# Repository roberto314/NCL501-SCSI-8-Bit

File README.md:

# NCL501-SCSI-8-Bit
Recreation of a bootable ISA 8-Bit SCSI Card.

There is one PAL on the Card (PAL16L8), it is protected unfortunately.
A dump has been done and the equations have been recreated.
They might be wrong.
BIOS EPROM is a 27C64 Type, RAM is not poplated but a 6116 might be used (24-pin Socket).

[Schematic](schematic/NCL501/pdf/NCL501.pdf)

The new card looks like this:

or the real thing:

Changes are:

* active termination or passive Termination possible.
* Term Power with Jumper
* DB25 Connector instead of DB37
* smaller (97.75 x 135mm)

For active Termination the following Parts are needed:

    - C12: 470p Footprint 1206

    - C13, C14: 100n Footprint 1206

    - U11: MIC5219 2.85V Regulator SOT-23-5

This Adapter has some serious shortcomings:

In my Computer (micro8088) it ONLY works with DRQ/DACK 3, ROM @ D8000 and IO @ 330!
IRQ doesn't matter also the RAM onboard is not necessary.

I tested the following Images:

Heads and Sectors working:

spf = sectors/fat, spc = sectors/cluster

* C:  79 / H:8  / S:32 10 MB (FAT12) works
* C:  95 / H:8  / S:32 12 MB (FAT12) works
* C:  39 / H:16 / S:32 10 MB works
* C:  22 / H:15 / S:63 10 MB doesn't work (non-system disk)
* C:  21 / H:16 / S:62 10 MB doesn't work (non-system disk)
* C:  21 / H:16 / S:63 10 MB doesn't work (non-system disk)
* C:  63 / H:16 / S:32 16 MB (FAT12) works
* C:  67 / H:16 / S:32 17 MB (FAT16/4) doesn't work (non-system disk)
* C:  67 / H:16 / S:32 17 MB (FAT16/4) with spf=0x40 instead of 0x100: works
* C: 127 / H:16 / S:32 32 MB (FAT16/4) with spf=0x40 instead of 0x100: works
* C: 135 / H:16 / S:32 33 MB (FAT16/6) with spf=0x60 instead of 0x100: works
* C: 255 / H:16 / S:32 64 MB (FAT16/6) with spf=0x40 instead of 0x100: doesn't work (non-system disk)
* C: 255 / H:16 / S:32 64 MB (FAT16/6) with spf=0x40 instead of 0x100: doesn't work (non-system disk)
* C: 255 / H:16 / S:32 64 MB (FAT16/6) with spf=0x80 instead of 0x100: works
* C: 507 / H:16 / S:32 127 MB (FAT16/6) with spf=0xFF instead of 0x100: doesn't work (non-system disk)
* C: 507 / H:16 / S:32 127 MB (FAT16/6) with spf=0xFE instead of 0x100: doesn't work (non-system disk)
* C: 359 / H:16 / S:32 90 MB (FAT16/6) with spf=0xC0 instead of 0x100, spc=4: doesn't work
* C: 359 / H:16 / S:32 90 MB (FAT16/6) with spf=0xC0 instead of 0x100, spc=8: doesn't work
* C: 183 / H:16 / S:63 90 MB (FAT16/6) with spf=0xC0 instead of 0x100: doesn't work (non-system disk)
* C: 359 / H:16 / S:32 90 MB (FAT16/6) with spf=0xD0 instead of 0x100: doesn't work, hangs
* C: 359 / H:16 / S:32 90 MB (FAT16/6) with spf=0xE0 instead of 0x100: doesn't work, hangs
* C: 479 / H:16 / S:32 120 MB (FAT16/6) with spf=0xF0 instead of 0x100: doesn't work (non-system disk)
* C: 511 / H:16 / S:32 128 MB (FAT16/6) with spf=0xC0 instead of 0x100: doesn't work
* C: 511 / H:16 / S:32 128 MB (FAT16/6) with spf=0x80, spc=8 instead of 0x100: works
* C: 515 / H:16 / S:32 129 MB (FAT16/6) with spf=0xC0 instead of 0x100: doesn't work
* C: 763 / H:16 / S:32 191 MB (FAT16/6) with spf=0xC0 instead of 0x100: doesn't work
* C: 767 / H:16 / S:32 192 MB (FAT16/6) with spf=0xC0 instead of 0x100: doesn't work
* C:1019 / H:16 / S:32 255 MB (FAT16/6) with spf=0x80,spc=16  works
* C:1023 / H:16 / S:32 256 MB (FAT16/6) with spf=0x80,spc=16  works
* C: 741 / H:16 / S:33 191 MB (FAT16/6) with spf=0xC0 instead of 0x100: doesn't work (non-system disk)
* C: 1006 / H:14 / S:48 330 MB (FAT16/6) with spf=0xC0 instead of 0x100: doesn't work (non-system disk)
* C:  510 / H:16 / S:48 191 MB (FAT16/6) with spf=0xC0 instead of 0x100: doesn't work (non-system disk)
* C:  620 / H:16 / S:62 300 MB (FAT16/6) with spf=0x100,spc=16: doesn't work (non-system disk)
* C:  620 / H:16 / S:62 300 MB (FAT16/6) with spf=0x80,spc=32: doesn't work (non-system disk)
* C:  620 / H:16 / S:62 300 MB (FAT16/6) with spf=0x80,spc=32: doesn't work (non-system disk)
* C:  262 / H:16 / S:63 300 MB (FAT16/6) with spf=0xFC,spc=16: doesn't work (non-system disk)
* C:  262 / H:16 / S:63 300 MB (FAT16/6) with spf=0xC0,spc=16: doesn't work (non-system disk)
* C:  514 / H:32 / S:32 257.5 MB (FAT16/6) with spf=0xFC,spc=16  works
* C: 1005 / H:32 / S:32 503 MB (FAT16/6) with spf=0xFC,spc=16  works
* C: 1001 / H:5 / S:52 127 MB (FAT16/6) with spf=0xC0,spc=8 doesn't work (non-system disk)
* C: 1001 / H:5 / S:52 127 MB (FAT16/6) with spf=0xFC,spc=8 doesn't work (non-system disk)
 
* C: 127 / H:16 / S:32 32 MB doesn't work (non-system disk)
* C: 479 / H:8  / S:32 60 MB doesn't work (non-system disk)
* C: 511 / H:8  / S:32 64 MB doesn't work (non-system disk)
* C: 197 / H:32 / S:32 99 MB (FAT16/4) with spf=0xC0 instead of 0x100: doesn't work (non-system disk)
* C:1023 / H:8  / S:32 128 MB doesn't work (non-system disk)
* C:1023 / H:16 / S:32 256 MB doesn't work (non-system disk)
* C:1019 / H:16 / S:32 255 MB doesn't work (non-system disk)
* C: 511 / H:16 / S:32 128 MB doesn't work (non-system disk)
* C: 511 / H:16 / S:32 128 MB (FAT16/4) with spf=0x40 instead of 0x100: doesn't work (non-system disk)
* C: 503 / H:16 / S:32 126 MB (FAT16/4) with spf=0x40 instead of 0x100: doesn't work (non-system disk)

Limits are: 

* spf Value only 8-bit and only some values are possible.
* Size 503MB for now.

The Card can be hacked to be a SUMO SCSI Card with reasonable effort (by omitting U12-14). Then the ASPI Driver ZHA.SYS and ZDRV.SYS will work.

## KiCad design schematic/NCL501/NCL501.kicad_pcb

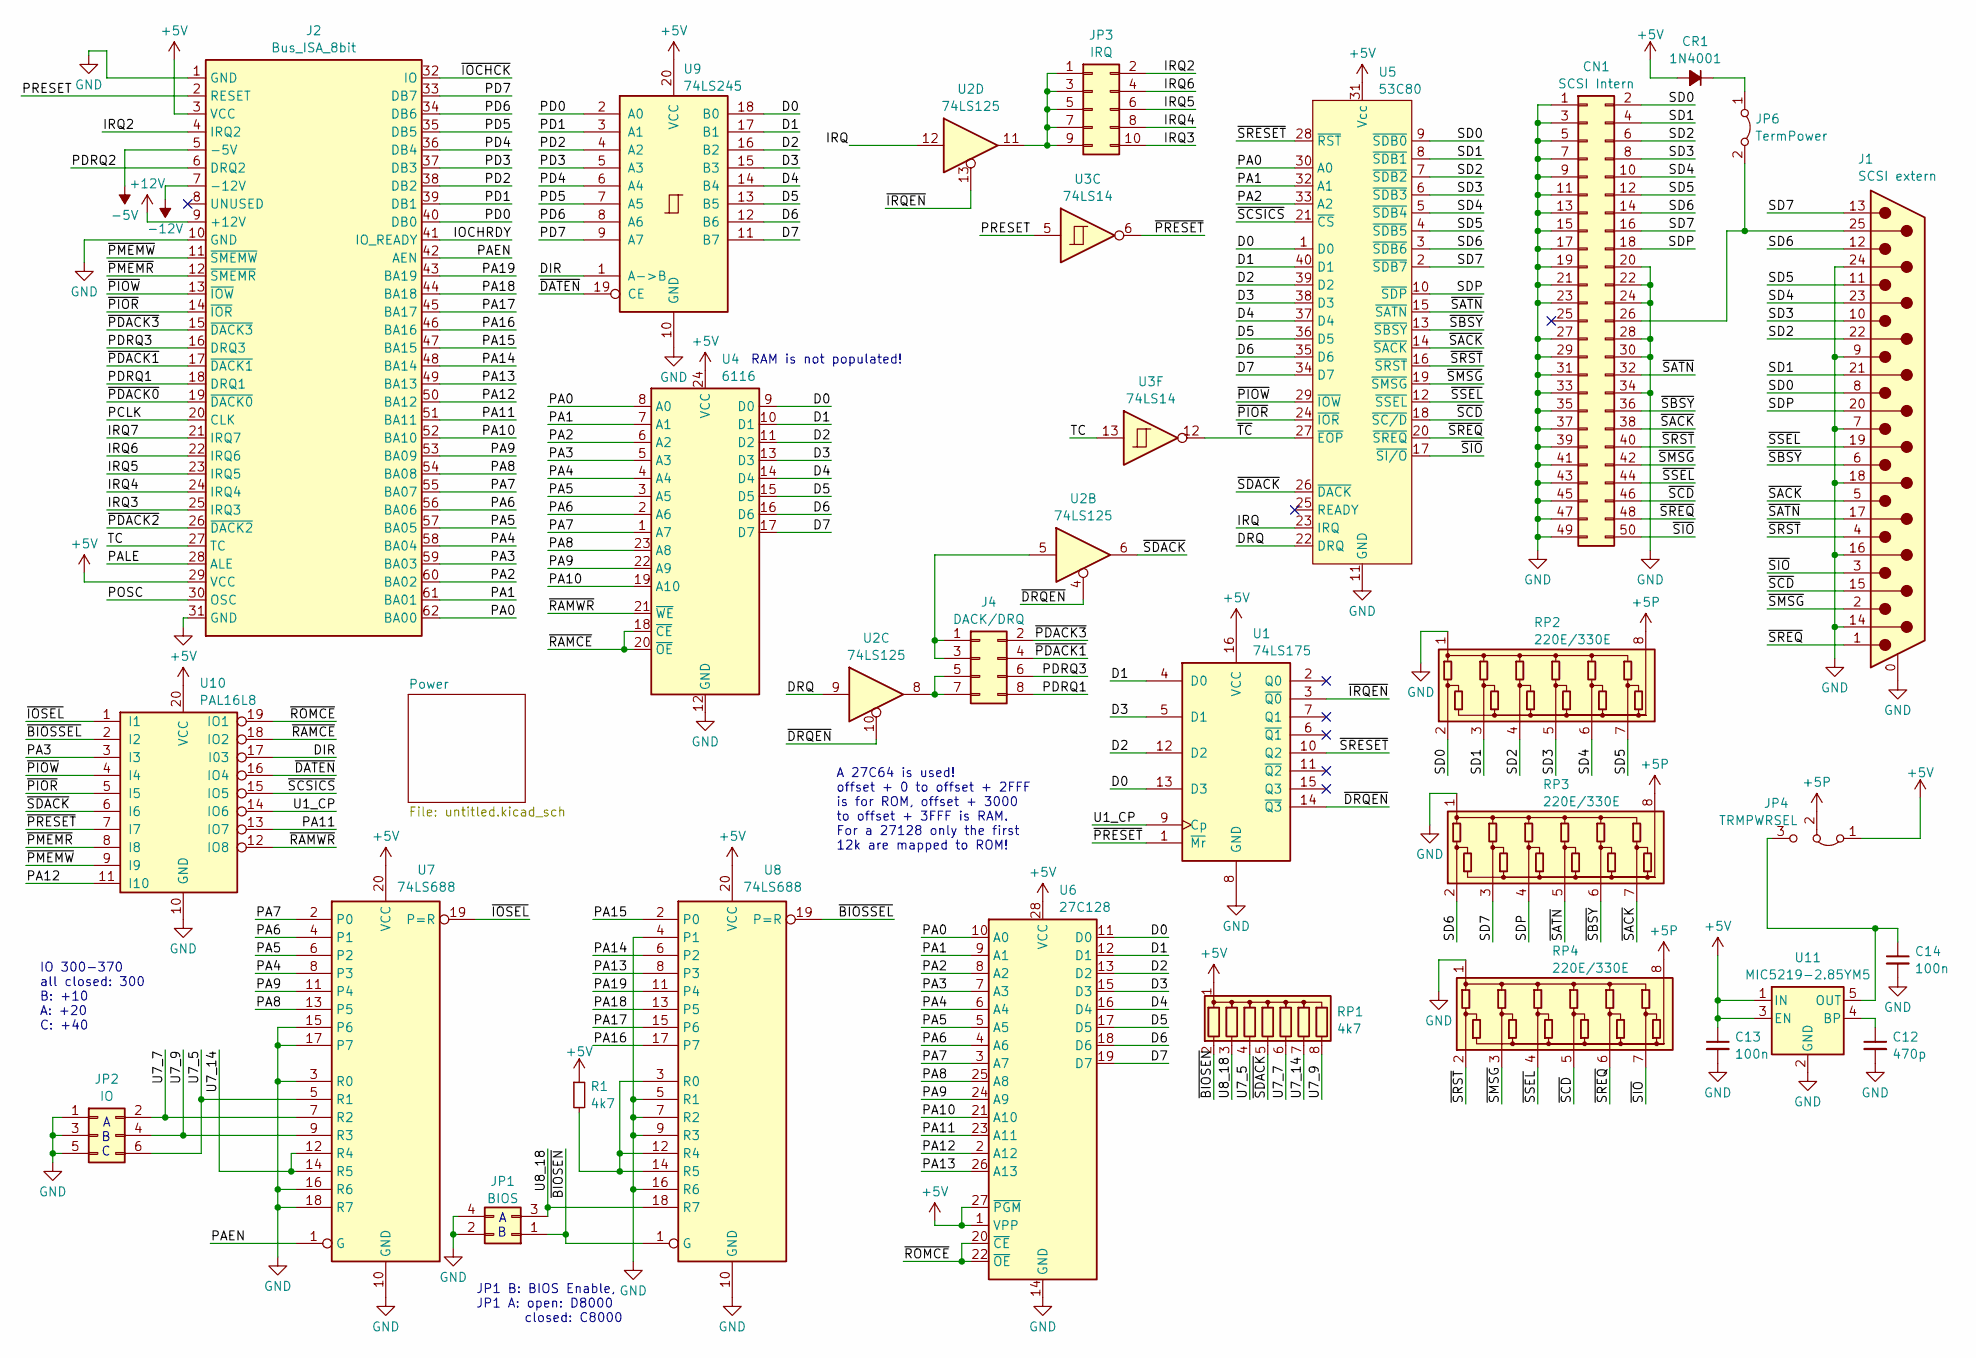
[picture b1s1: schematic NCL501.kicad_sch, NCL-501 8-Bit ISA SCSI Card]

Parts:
C12: 470p; C_1206_3216Metric_Pad1.33x1.80mm_HandSolder
C13, C14: 100n; C_1206_3216Metric_Pad1.33x1.80mm_HandSolder
CN1: SCSI Intern; PinHeader_2x25_P2.54mm_Vertical
CR1: 1N4001; D_DO-34_SOD68_P12.70mm_Horizontal
J1: SCSI extern; DSUB-25_Female_Horizontal_P2.77x2.84mm_EdgePinOffset7.70mm_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
J2: Bus_ISA_8bit; BUS_XT
J4: DACK/DRQ; PinHeader_2x04_P2.54mm_Vertical
JP1: BIOS; PinHeader_2x02_P2.54mm_Vertical
JP2: IO; PinHeader_2x03_P2.54mm_Vertical
JP3: IRQ; PinHeader_2x05_P2.54mm_Vertical
JP4: TRMPWRSEL; SolderJumper-3_P1.3mm_Bridged12_RoundedPad1.0x1.5mm
JP6: TermPower; PinHeader_1x02_P2.54mm_Vertical
R1: 4k7; R_Axial_DIN0309_L9.0mm_D3.2mm_P12.70mm_Horizontal
RP1: 4k7; R_Array_SIP8
RP2, RP3, RP4: 220E/330E; R_Array_SIP8
U1: 74LS175; DIP-16_W7.62mm
U2: 74LS125; DIP-14_W7.62mm
U3: 74LS14; DIP-14_W7.62mm
U4: 6116; DIP-24_W15.24mm
U5: 53C80; DIP-40_W15.24mm
U6: 27C128; DIP-28_W15.24mm
U7, U8: 74LS688; DIP-20_W7.62mm
U9: 74LS245; DIP-20_W7.62mm_LongPads
U10: PAL16L8; DIP-20_W7.62mm
U11: MIC5219-2.85YM5; SOT-23-5

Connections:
+5P: JP4.2 (C), RP2.8 (COM2), RP3.8 (COM2), RP4.8 (COM2)
+5V: C13.1, CR1.2 (A), J2.3 (VCC), J2.29 (VCC), JP4.1 (A), R1.1, RP1.1 (common), U1.16 (VCC), U4.24 (VCC), U5.31 (Vcc), U6.1 (VPP), U6.27 (~PGM), U6.28 (VCC), U7.20 (VCC), U8.20 (VCC), U9.20 (VCC), U10.20 (VCC), U11.1 (IN), U11.3 (EN); also elsewhere on the board
+12V: J2.9 (+12V)
-5V: J2.5 (-5V)
-12V: J2.7 (-12V)
/D0: U1.13 (D3), U4.9 (D0), U5.1 (D0), U6.11 (D0), U9.18 (B0)
/D1: U1.4 (D0), U4.10 (D1), U5.40 (D1), U6.12 (D1), U9.17 (B1)
/D2: U1.12 (D2), U4.11 (D2), U5.39 (D2), U6.13 (D2), U9.16 (B2)
/D3: U1.5 (D1), U4.13 (D3), U5.38 (D3), U6.15 (D3), U9.15 (B3)
/D4: U4.14 (D4), U5.37 (D4), U6.16 (D4), U9.14 (B4)
/D5: U4.15 (D5), U5.36 (D5), U6.17 (D5), U9.13 (B5)
/D6: U4.16 (D6), U5.35 (D6), U6.18 (D6), U9.12 (B6)
/D7: U4.17 (D7), U5.34 (D7), U6.19 (D7), U9.11 (B7)
/DIR: U9.1 (A->B), U10.17 (I03)
/DRQ: U2.9, U5.22 (DRQ)
/IOCHRDY: J2.41 (IO_READY)
/IRQ: U2.12, U5.23 (IRQ)
/IRQ2: J2.4 (IRQ2), JP3.2
/IRQ3: J2.25 (IRQ3), JP3.10
/IRQ4: J2.24 (IRQ4), JP3.8
/IRQ5: J2.23 (IRQ5), JP3.6
/IRQ6: J2.22 (IRQ6), JP3.4
/IRQ7: J2.21 (IRQ7)
/PA0: J2.62 (BA00), U4.8 (A0), U5.30 (A0), U6.10 (A0)
/PA1: J2.61 (BA01), U4.7 (A1), U5.32 (A1), U6.9 (A1)
/PA2: J2.60 (BA02), U4.6 (A2), U5.33 (A2), U6.8 (A2)
/PA3: J2.59 (BA03), U4.5 (A3), U6.7 (A3), U10.3 (I3)
/PA4: J2.58 (BA04), U4.4 (A4), U6.6 (A4), U7.8 (P3)
/PA5: J2.57 (BA05), U4.3 (A5), U6.5 (A5), U7.6 (P2)
/PA6: J2.56 (BA06), U4.2 (A6), U6.4 (A6), U7.4 (P1)
/PA7: J2.55 (BA07), U4.1 (A7), U6.3 (A7), U7.2 (P0)
/PA8: J2.54 (BA08), U4.23 (A8), U6.25 (A8), U7.13 (P5)
/PA9: J2.53 (BA09), U4.22 (A9), U6.24 (A9), U7.11 (P4)
/PA10: J2.52 (BA10), U4.19 (A10), U6.21 (A10)
/PA11: J2.51 (BA11), U6.23 (A11), U10.13 (IO7)
/PA12: J2.50 (BA12), U6.2 (A12), U10.11 (I10)
/PA13: J2.49 (BA13), U6.26 (A13), U8.8 (P3)
/PA14: J2.48 (BA14), U8.6 (P2)
/PA15: J2.47 (BA15), U8.2 (P0)
/PA16: J2.46 (BA16), U8.17 (P7)
/PA17: J2.45 (BA17), U8.15 (P6)
/PA18: J2.44 (BA18), U8.13 (P5)
/PA19: J2.43 (BA19), U8.11 (P4)
/PAEN: J2.42 (AEN), U7.1 (G)
/PALE: J2.28 (ALE)
/PCLK: J2.20 (CLK)
/PD0: J2.40 (DB0), U9.2 (A0)
/PD1: J2.39 (DB1), U9.3 (A1)
/PD2: J2.38 (DB2), U9.4 (A2)
/PD3: J2.37 (DB3), U9.5 (A3)
/PD4: J2.36 (DB4), U9.6 (A4)
/PD5: J2.35 (DB5), U9.7 (A5)
/PD6: J2.34 (DB6), U9.8 (A6)
/PD7: J2.33 (DB7), U9.9 (A7)
/PDRQ1: J2.18 (DRQ1), J4.8
/PDRQ2: J2.6 (DRQ2)
/PDRQ3: J2.16 (DRQ3), J4.6
/POSC: J2.30 (OSC)
/PRESET: J2.2 (RESET), U3.5
/SD0: CN1.2, J1.8, RP2.2 (R1), U5.9 (~SDB0)
/SD1: CN1.4, J1.21, RP2.3 (R2), U5.8 (~SDB1)
/SD2: CN1.6, J1.22, RP2.4 (R3), U5.7 (~SDB2)
/SD3: CN1.8, J1.10, RP2.5 (R4), U5.6 (~SDB3)
/SD4: CN1.10, J1.23, RP2.6 (R5), U5.5 (~SDB4)
/SD5: CN1.12, J1.11, RP2.7 (R6), U5.4 (~SDB5)
/SD6: CN1.14, J1.12, RP3.2 (R1), U5.3 (~SDB6)
/SD7: CN1.16, J1.13, RP3.3 (R2), U5.2 (~SDB7)
/SDP: CN1.18, J1.20, RP3.4 (R3), U5.10 (~SDP)
/TC: J2.27 (TC), U3.13
/U1_CP: U1.9 (Cp), U10.14 (IO6)
/U7_5: JP2.6, RP1.4 (R3), U7.5 (R1)
/U7_7: JP2.2, RP1.6 (R5), U7.7 (R2)
/U7_9: JP2.4, RP1.8 (R7), U7.9 (R3)
/U7_14: RP1.7 (R6), U7.12 (R4), U7.14 (R5)
/U8_18: JP1.3, RP1.3 (R2), U8.18 (R7)
/~BIOSEN: JP1.1, RP1.2 (R1), U8.1 (G)
/~BIOSSEL: U8.19 (P=R), U10.2 (I2)
/~DATEN: U9.19 (CE), U10.16 (IO4)
/~DRQEN: U1.14 (~Q3), U2.4, U2.10
/~IOCHCK: J2.32 (IO)
/~IOSEL: U7.19 (P=R), U10.1 (I1)
/~IRQEN: U1.3 (~Q0), U2.13
/~PDACK0: J2.19 (~DACK0)
/~PDACK1: J2.17 (~DACK1), J4.4
/~PDACK2: J2.26 (~DACK2)
/~PDACK3: J2.15 (~DACK3), J4.2
/~PIOR: J2.14 (~IOR), U5.24 (~IOR), U10.5 (I5)
/~PIOW: J2.13 (~IOW), U5.29 (~IOW), U10.4 (I4)
/~PMEMR: J2.12 (~SMEMR), U10.8 (I8)
/~PMEMW: J2.11 (~SMEMW), U10.9 (I9)
/~PRESET: U1.1 (~Mr), U3.6, U10.7 (I7)
/~RAMCE: U4.18 (~CE), U4.20 (~OE), U10.18 (IO2)
/~RAMWR: U4.21 (~WE), U10.12 (IO8)
/~ROMCE: U6.20 (~CE), U6.22 (~OE), U10.19 (IO1)
/~SACK: CN1.38, J1.5, RP3.7 (R6), U5.14 (~SACK)
/~SATN: CN1.32, J1.17, RP3.5 (R4), U5.15 (~SATN)
/~SBSY: CN1.36, J1.6, RP3.6 (R5), U5.13 (~SBSY)
/~SCD: CN1.46, J1.15, RP4.5 (R4), U5.18 (~SC/D)
/~SCSICS: U5.21 (~CS), U10.15 (IO5)
/~SDACK: RP1.5 (R4), U2.6, U5.26 (~DACK), U10.6 (I6)
/~SIO: CN1.50, J1.3, RP4.7 (R6), U5.17 (~SI/O)
/~SMSG: CN1.42, J1.2, RP4.3 (R2), U5.19 (~SMSG)
/~SREQ: CN1.48, J1.1, RP4.6 (R5), U5.20 (~SREQ)
/~SRESET: U1.10 (Q2), U5.28 (~RST)
/~SRST: CN1.40, J1.4, RP4.2 (R1), U5.16 (~SRST)
/~SSEL: CN1.44, J1.19, RP4.4 (R3), U5.12 (~SSEL)
/~TC: U3.12, U5.27 (~EOP)
GND: C12.2, C13.2, C14.2, CN1.1, CN1.3, CN1.5, CN1.7, CN1.9, CN1.11, CN1.13, CN1.15, CN1.17, CN1.19, CN1.20, CN1.21, CN1.22, CN1.23, CN1.24, CN1.27, CN1.28, CN1.29, CN1.30, CN1.31, CN1.33, CN1.34, CN1.35, CN1.37, CN1.39, CN1.41, CN1.43, CN1.45, CN1.47, CN1.49, J1.0 (PAD), J1.7, J1.9, J1.14, J1.16, J1.18, J1.24, J2.1 (GND), J2.10 (GND), J2.31 (GND), JP1.2, JP1.4, JP2.1, JP2.3, JP2.5, RP2.1 (COM1), RP3.1 (COM1), RP4.1 (COM1), U1.8 (GND), U4.12 (GND), U5.11 (GND), U6.14 (GND), U7.3 (R0), U7.10 (GND), U7.15 (P6), U7.16 (R6), U7.17 (P7), U7.18 (R7), U8.4 (P1), U8.5 (R1), U8.7 (R2), U8.9 (R3), U8.10 (GND), U8.16 (R6), U9.10 (GND), U10.10 (GND), U11.2 (GND); also elsewhere on the board
unnamed: CN1.26, J1.25, JP6.2 (B)
unnamed: CR1.1 (K), JP6.1 (A)
unnamed: J4.1, J4.3, U2.5
unnamed: J4.5, J4.7, U2.8
unnamed: JP3.1, JP3.3, JP3.5, JP3.7, JP3.9, U2.11
unnamed: C14.1, JP4.3 (B), U11.5 (OUT)
unnamed: R1.2, U8.3 (R0), U8.12 (R4), U8.14 (R5)
unnamed: C12.1, U11.4 (BP)

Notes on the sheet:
A B C
RAM is not populated!
IO 300-370 all closed: 300 B: +10 A: +20 C: +40
A 27C64 is used! offset + 0 to offset + 2FFF is for ROM, offset + 3000 to offset + 3FFF is RAM. For a 27128 only the first 12k are mapped to ROM!
JP1 B: BIOS Enable, JP1 A: open: D8000 closed: C8000
A B

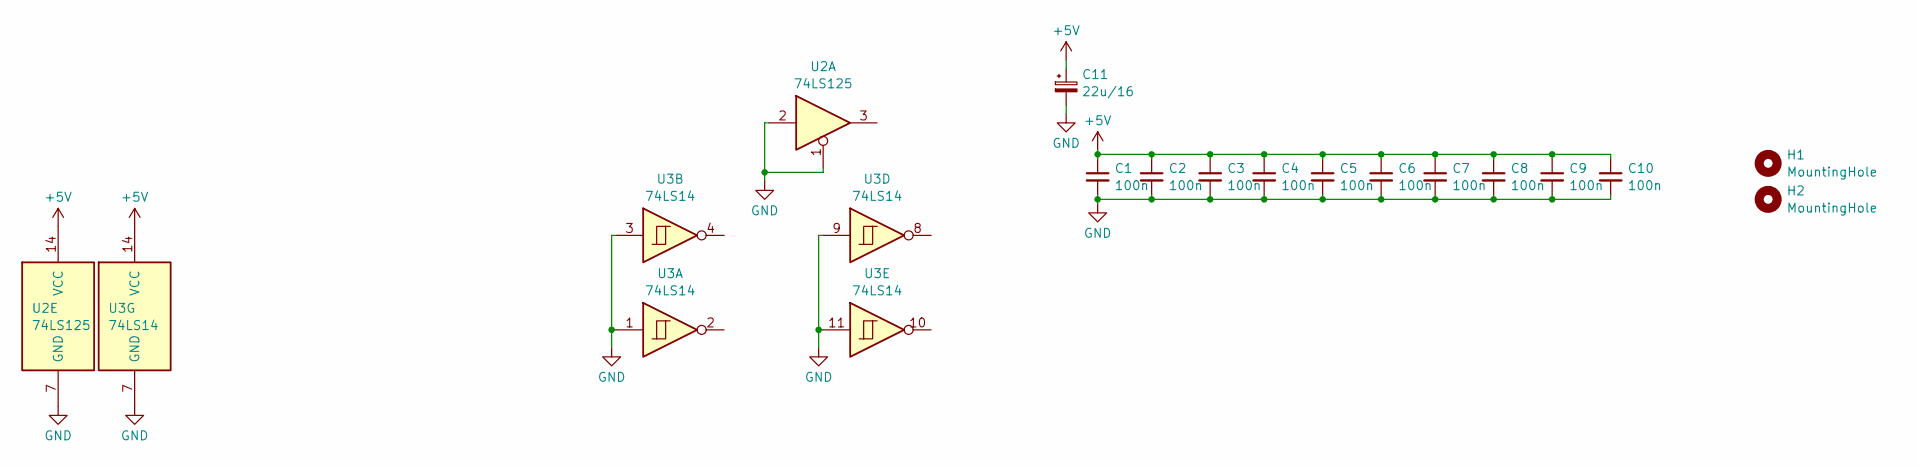
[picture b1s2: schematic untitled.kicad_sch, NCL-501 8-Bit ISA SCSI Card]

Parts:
C1, C2, C3, C4, C5, C6, C7, C8, C9, C10: 100n; C_Disc_D8.0mm_W2.5mm_P5.00mm
C11: 22u/16; CP_Axial_L11.0mm_D5.0mm_P18.00mm_Horizontal
H1, H2: MountingHole; MountingHole_3.5mm
U2: 74LS125; DIP-14_W7.62mm
U3: 74LS14; DIP-14_W7.62mm

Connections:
+5V: C1.1, C2.1, C3.1, C4.1, C5.1, C6.1, C7.1, C8.1, C9.1, C10.1, C11.1, U2.14 (VCC), U3.14 (VCC); also elsewhere on the board
GND: C1.2, C2.2, C3.2, C4.2, C5.2, C6.2, C7.2, C8.2, C9.2, C10.2, C11.2, U2.1, U2.2, U2.7 (GND), U3.1, U3.3, U3.7 (GND), U3.9, U3.11; also elsewhere on the board

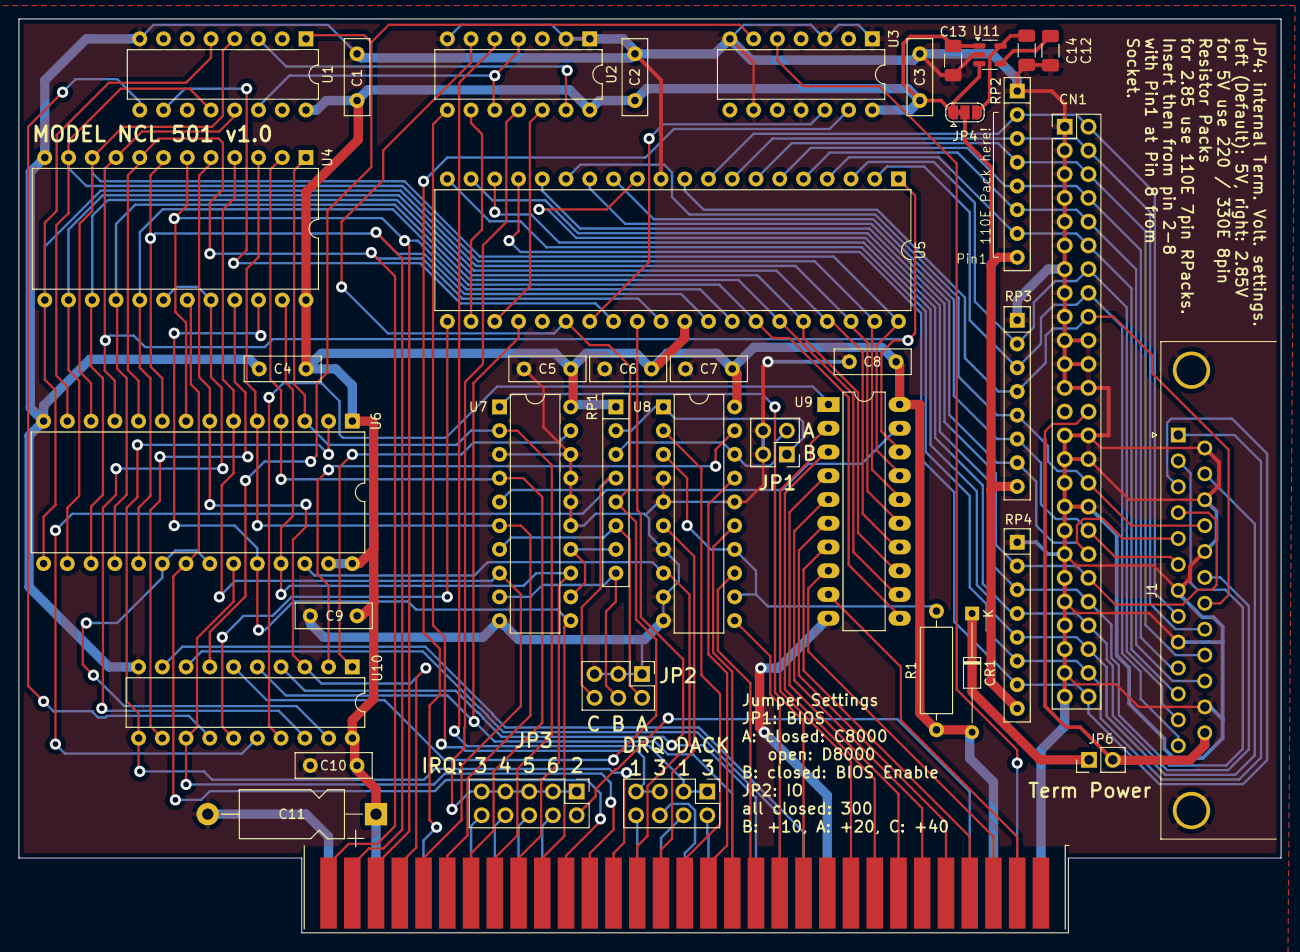
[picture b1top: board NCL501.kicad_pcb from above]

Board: 2 copper layers, 135.0 x 97.8 mm, 42 parts (0 on the bottom side), 104 nets.

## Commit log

2024-04-10 initial
2024-04-11 first manufactured Version
2024-04-11 pics updated
2024-04-11 Readme updated
2024-04-11 Schematic updated
2024-04-13 manufacturing data update
2024-04-23 card works, more testing needed
2024-04-23 Readme update
2024-04-26 more images tested, 256MB is max now
2024-04-28 more images tested, 503MB is max now
2024-05-11 Pics added
2024-05-11 Pics and description added
2024-05-14 test with sumo bios
